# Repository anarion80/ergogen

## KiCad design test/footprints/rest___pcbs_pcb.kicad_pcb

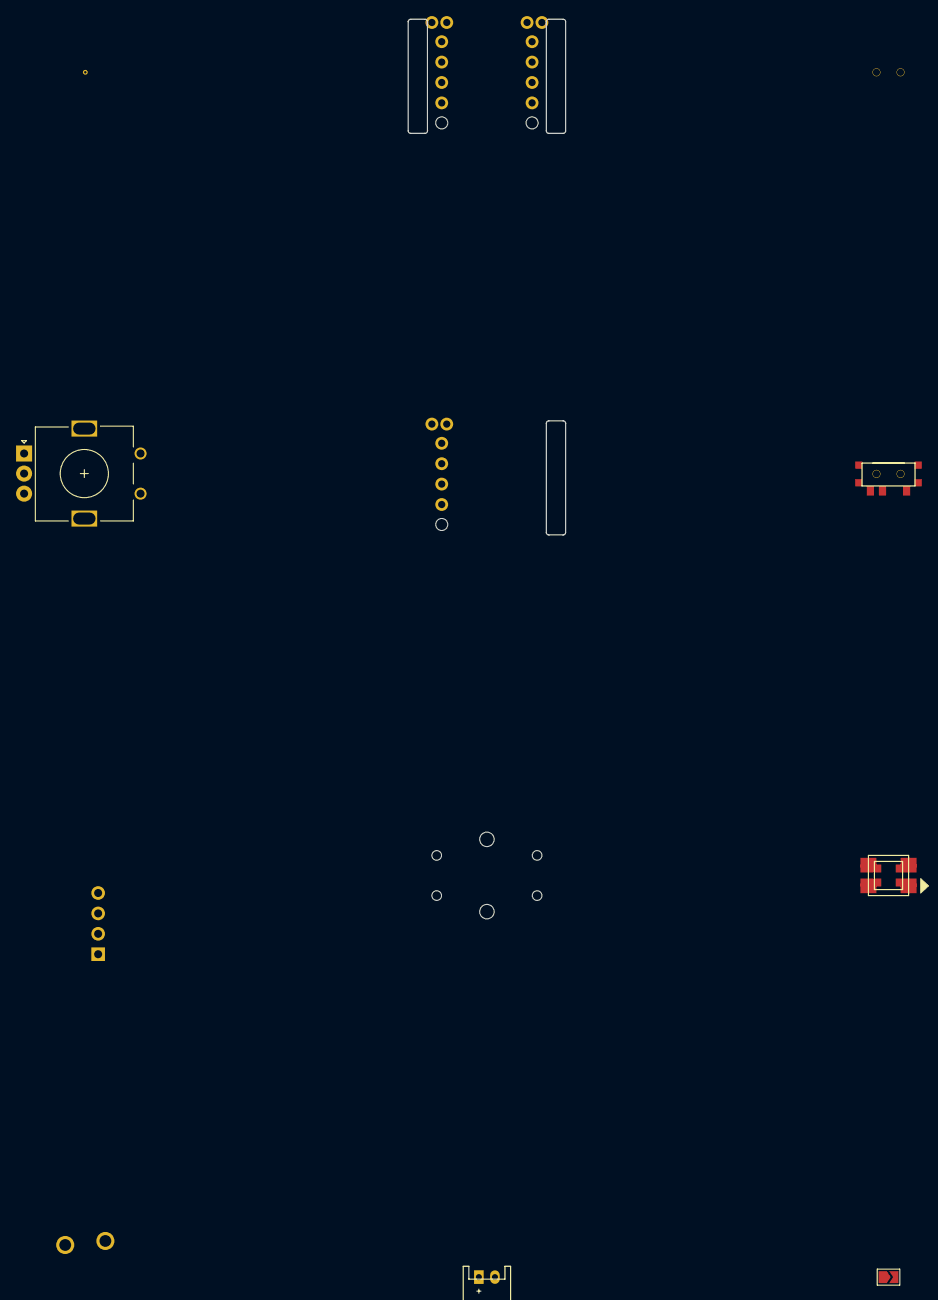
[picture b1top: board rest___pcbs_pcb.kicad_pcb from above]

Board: 2 copper layers, 10 parts (0 on the bottom side), 6 nets, no tracks yet.

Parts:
J1: Jumper; SolderJumper-2_P1.3mm_Open_TrianglePad1.0x1.5mm
JST1: JST_PH_S2B-PH-K_02x2.00mm_Angled
LED1: WS2812B
OLED1: OLED; OLED_headers
ROT1: rotary_encoder
S1: ALPS
S2: OMRON_B3F-4055
T1, T2: SPDT_C128955
_1: VIA-0.6mm

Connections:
GND: LED1.3, LED1.33, OLED1.1
VCC: LED1.1, LED1.11, OLED1.2
din: LED1.4, LED1.44
dout: LED1.2, LED1.22
from: J1.1, ROT1.1, S1.1, S2.1, S2.2, T1.1, T2.1
to: J1.2, ROT1.2, S1.2, S2.3, S2.4, T1.2, T2.2

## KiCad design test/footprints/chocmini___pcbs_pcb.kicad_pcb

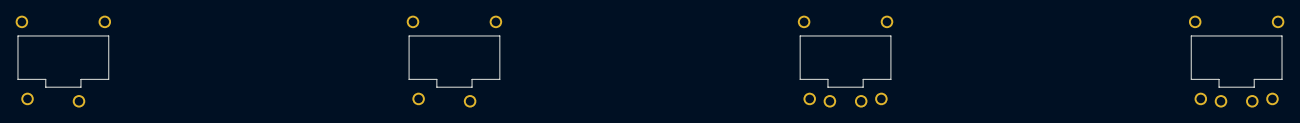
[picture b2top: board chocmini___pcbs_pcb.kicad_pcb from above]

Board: 2 copper layers, 4 parts (0 on the bottom side), 2 nets, no tracks yet.

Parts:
S1, S2, S3, S4: Kailh_PG1232

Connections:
from: S1.1, S2.1, S3.1, S4.1
to: S1.2, S2.2, S3.2, S4.2

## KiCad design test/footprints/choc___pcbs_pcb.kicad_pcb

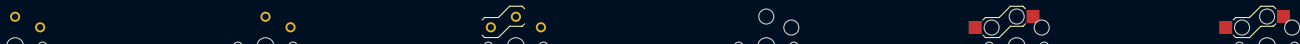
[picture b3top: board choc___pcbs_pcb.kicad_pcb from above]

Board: 2 copper layers, 6 parts (0 on the bottom side), 2 nets, no tracks yet.

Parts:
S1, S2, S3, S4, S5, S6: PG1350

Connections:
from: S1.1, S2.1, S3.1, S4.1, S5.1, S6.1
to: S1.2, S2.2, S3.2, S4.2, S5.2, S6.2

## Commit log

2023-07-06 Update side indicator
2023-09-08 ✅ Fix tests
2023-09-09 Update to Kicad 7 format
2023-09-09 Update format to Kicad 7 - continued
2023-09-12 Update promicro_pretty to not error on DRC
2023-09-12 Update b3u1000ps footprint to be aligned side-agnostic
2023-09-12 Added niceview, oled and others footprints
2023-09-12 Update footprints so that pcbdraw still works
2023-09-17 Make side indicator centered
2023-09-18 ⏪️ Revert the Kicad7 alignment for side indicator
2023-09-18 Add references for iBOM to footprints
2023-09-28 Remove silkscreen from Jumper
2023-09-28 Update jumper footprint
